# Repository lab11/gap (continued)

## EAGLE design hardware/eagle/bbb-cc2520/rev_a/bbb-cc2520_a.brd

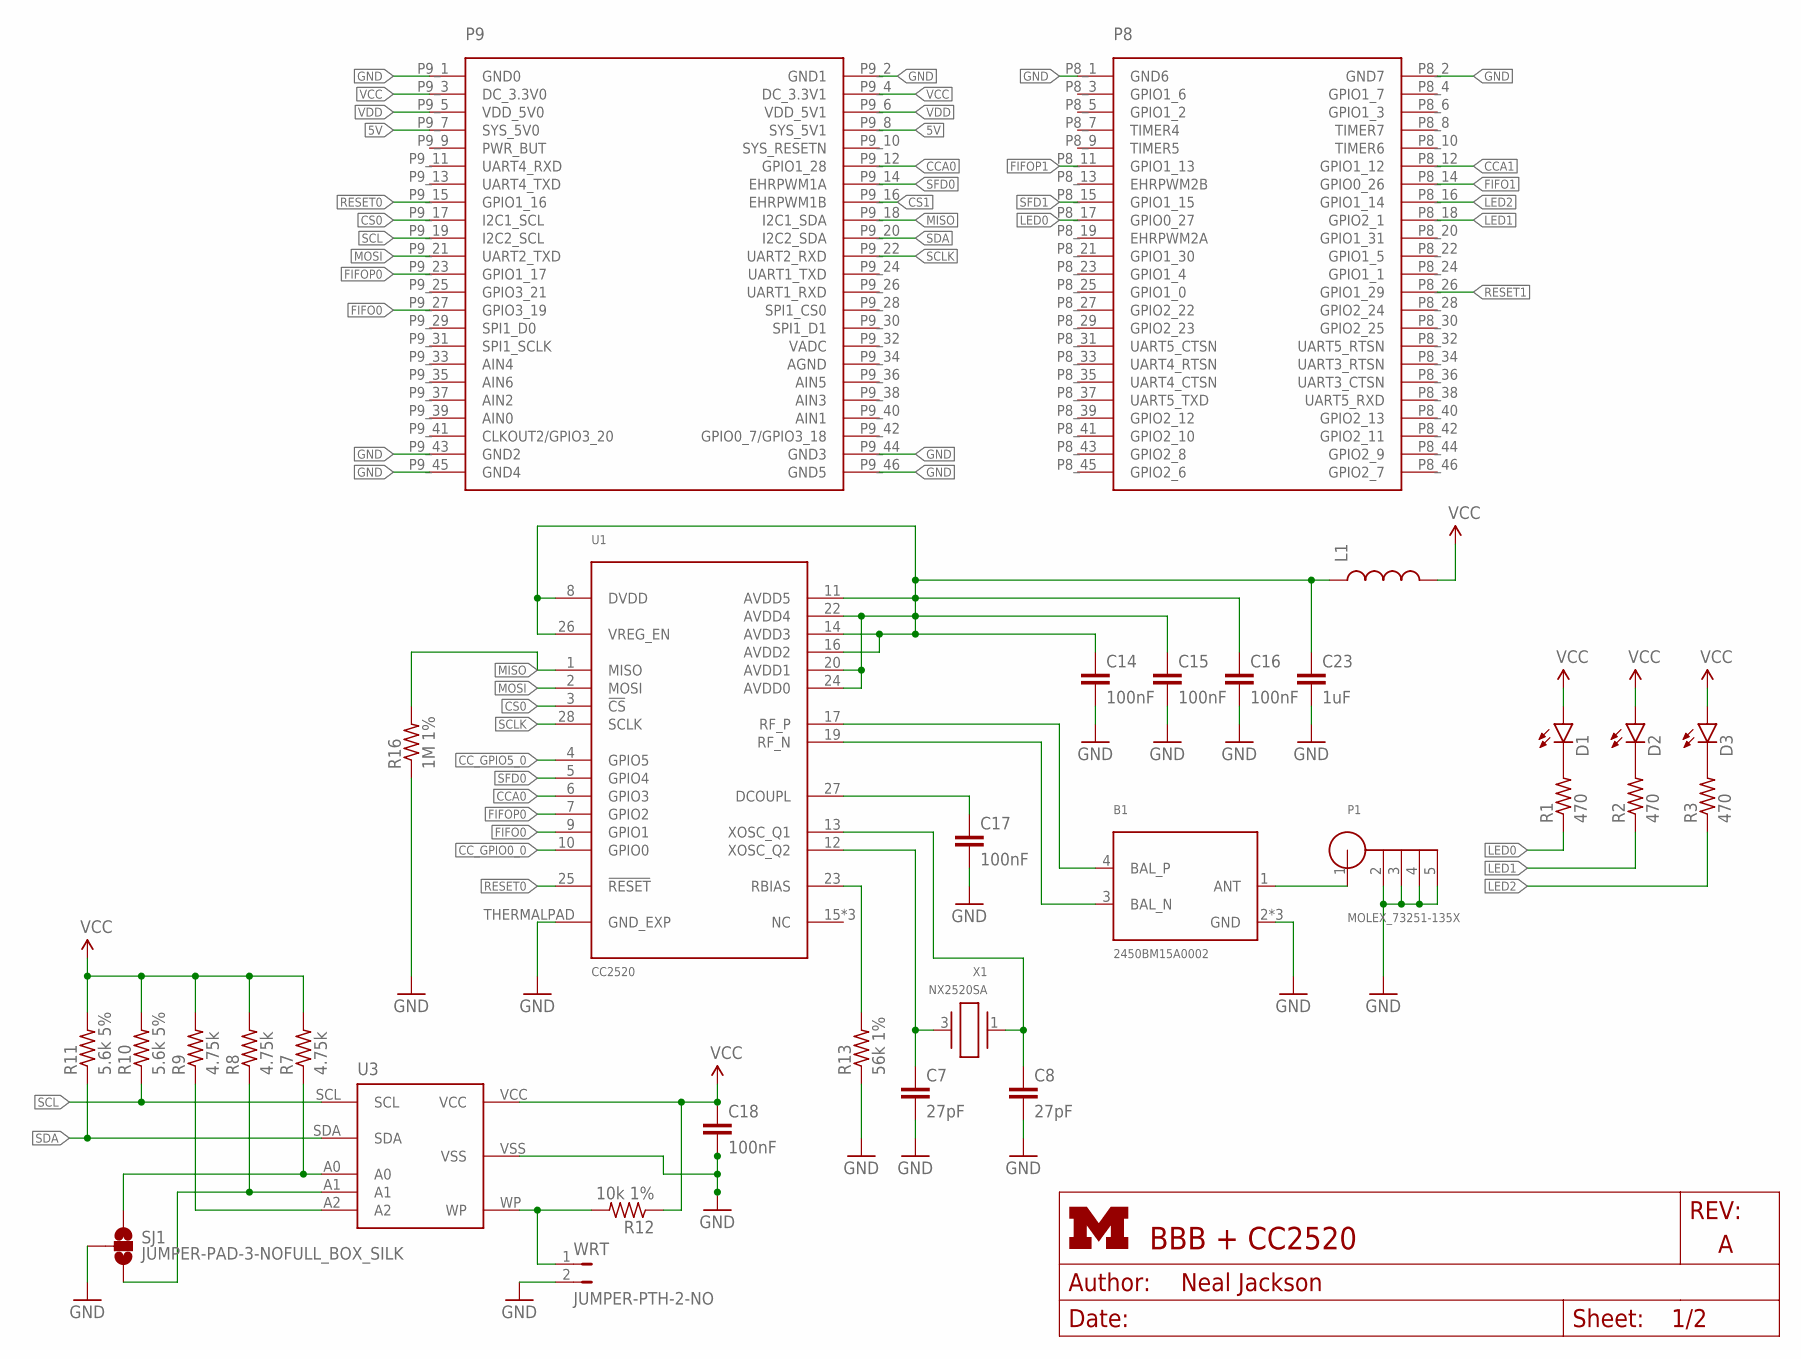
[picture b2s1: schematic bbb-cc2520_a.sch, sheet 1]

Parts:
B1: 2450BM15A0002; 2450BM
C7, C8: 27pF; C0402; DIGIKEY 490-5869-1-ND
C14, C15, C16, C17, C18: 100nF; C0402; DIGIKEY 490-1318-1-ND
C23: 1uF; C0603; DIGIKEY 490-1550-1-ND
D1: LED0603; LED-0603; DIGIKEY 160-1834-1-ND
D2: LED0603; LED-0603; DIGIKEY 160-1835-1-ND
D3: LED0603; LED-0603; DIGIKEY 160-1837-1-ND
L1: INDUCTOR0603; 0603; DIGIKEY 490-1015-1-ND
P1: MOLEX_73251-135X; SMA-J/PCB
P9/P8: BBB_HEADERS
R1, R2, R3: 470; R0402; DIGIKEY RHM470JCT-ND
R7, R8, R9: 4.75k; R0402; DIGIKEY RHM1.00MCDCT-ND
R10, R11: 5.6k 5%; R0402; DIGIKEY RHM1.00MCDCT-ND
R12: 10k 1%; R0402; DIGIKEY RHM1.00MCDCT-ND
R13: 56k 1%; R0402; DIGIKEY P56.0KLCT-ND
R16: 1M 1%; R0402; DIGIKEY RHM1.00MCDCT-ND
SJ1: JUMPER-PAD-3-NOFULL_BOX_SILK; PAD-JUMPER-3-NO_YES_SILK_FULL_BOX
U1: CC2520; S-PVQFN-N28
U3: CAT24C256WI-GT3
WRT: JUMPER-PTH-2-NO; PTH-JUMPER-2-NO_NO_SILK
X1: NX2520SA

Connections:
5V: P9/P8.P9_7 (SYS_5V0), P9/P8.P9_8 (SYS_5V1)
!RESET0: P9/P8.P9_15 (GPIO1_16), U1.25 (!RESET)
!RESET1: P9/P8.P8_26 (GPIO1_29); also elsewhere on the board
CCA0: P9/P8.P9_12 (GPIO1_28), U1.6 (GPIO3)
CCA1: P9/P8.P8_12 (GPIO1_12); also elsewhere on the board
CC_GPIO0_0: U1.10 (GPIO0)
CC_GPIO5_0: U1.4 (GPIO5)
CS0: P9/P8.P9_17 (I2C1_SCL), U1.3 (!CS)
CS1: P9/P8.P9_16 (EHRPWM1B); also elsewhere on the board
FIFO0: P9/P8.P9_27 (GPIO3_19), U1.9 (GPIO1)
FIFO1: P9/P8.P8_14 (GPIO0_26); also elsewhere on the board
FIFOP0: P9/P8.P9_23 (GPIO1_17), U1.7 (GPIO2)
FIFOP1: P9/P8.P8_11 (GPIO1_13); also elsewhere on the board
GND: B1.2 (GND), B1.5 (GND), B1.6 (GND), C7.2, C8.2, C14.2, C15.2, C16.2, C17.2, C18.2, C23.2, P1.2, P1.3, P1.4, P1.5, P9/P8.P8_1 (GND6), P9/P8.P8_2 (GND7), P9/P8.P9_1 (GND0), P9/P8.P9_2 (GND1), P9/P8.P9_43 (GND2), P9/P8.P9_44 (GND3), P9/P8.P9_45 (GND4), P9/P8.P9_46 (GND5), R13.1, R16.1, SJ1.2, U1.THERMALPAD (GND_EXP), U3.VSS, WRT.2; also elsewhere on the board
LED0: P9/P8.P8_17 (GPIO0_27), R1.1
LED1: P9/P8.P8_18 (GPIO2_1), R2.1
LED2: P9/P8.P8_16 (GPIO1_14), R3.1
MISO: P9/P8.P9_18 (I2C1_SDA), R16.2, U1.1 (MISO); also elsewhere on the board
MOSI: P9/P8.P9_21 (UART2_TXD), U1.2 (MOSI); also elsewhere on the board
unnamed: D1.C, R1.2
unnamed: D2.C, R2.2
unnamed: D3.C, R3.2
unnamed: C14.1, C15.1, C16.1, C23.1, L1.1, U1.8 (DVDD), U1.11 (AVDD5), U1.14 (AVDD3), U1.16 (AVDD2), U1.20 (AVDD1), U1.22 (AVDD4), U1.24 (AVDD0), U1.26 (VREG_EN)
unnamed: B1.1 (ANT), P1.1
unnamed: C8.1, U1.13 (XOSC_Q1), X1.1
unnamed: C17.1, U1.27 (DCOUPL)
unnamed: C7.1, U1.12 (XOSC_Q2), X1.3 (2)
unnamed: R13.2, U1.23 (RBIAS)
unnamed: R7.1, SJ1.1, U3.A0
unnamed: R8.1, SJ1.3, U3.A1
unnamed: R12.2, U3.WP, WRT.1
unnamed: R9.1, U3.A2
RF_N: B1.3 (BAL_N), U1.19 (RF_N)
RF_P: B1.4 (BAL_P), U1.17 (RF_P)
SCL: P9/P8.P9_19 (I2C2_SCL), R10.1, U3.SCL
SCLK: P9/P8.P9_22 (UART2_RXD), U1.28 (SCLK); also elsewhere on the board
SDA: P9/P8.P9_20 (I2C2_SDA), R11.1, U3.SDA
SFD0: P9/P8.P9_14 (EHRPWM1A), U1.5 (GPIO4)
SFD1: P9/P8.P8_15 (GPIO1_15); also elsewhere on the board
VCC: C18.1, D1.A, D2.A, D3.A, L1.2, P9/P8.P9_3 (DC_3.3V0), P9/P8.P9_4 (DC_3.3V1), R7.2, R8.2, R9.2, R10.2, R11.2, R12.1, U3.VCC; also elsewhere on the board
VDD: P9/P8.P9_5 (VDD_5V0), P9/P8.P9_6 (VDD_5V1)

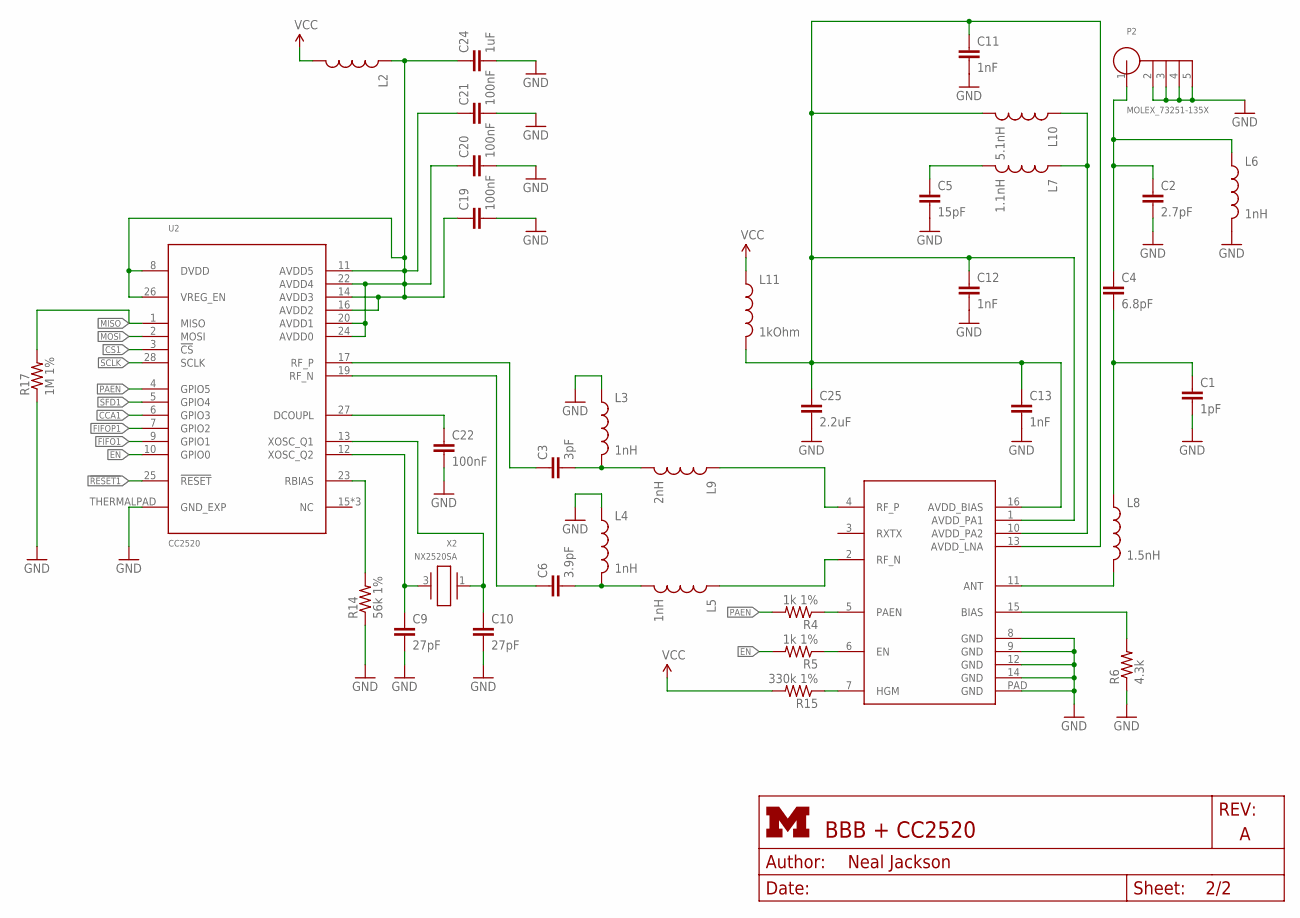
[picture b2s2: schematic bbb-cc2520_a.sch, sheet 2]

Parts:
C1: 1pF; C0402; DIGIKEY 490-1318-1-ND
C2: 2.7pF; C0402; DIGIKEY 490-1318-1-ND
C3: 3pF; C0402; DIGIKEY 490-1318-1-ND
C4: 6.8pF; C0402; DIGIKEY 490-1318-1-ND
C5: 15pF; C0402; DIGIKEY 490-1318-1-ND
C6: 3.9pF; C0402; DIGIKEY 490-1318-1-ND
C9, C10: 27pF; C0402; DIGIKEY 490-5869-1-ND
C11, C12, C13: 1nF; C0402; DIGIKEY 490-1318-1-ND
C19, C20, C21, C22: 100nF; C0402; DIGIKEY 490-1318-1-ND
C24: 1uF; C0603; DIGIKEY 490-1550-1-ND
C25: 2.2uF; C0402; DIGIKEY 490-1318-1-ND
L2: INDUCTOR0603; 0603; DIGIKEY 490-1015-1-ND
L3, L4, L5, L6: 1nH; C0402
L7: 1.1nH; C0402
L8: 1.5nH; C0402
L9: 2nH; C0402
L10: 5.1nH; C0402
L11: 1kOhm; C0402
P2: MOLEX_73251-135X; SMA-J/PCB
R4, R5: 1k 1%; R0402; DIGIKEY P56.0KLCT-ND
R6: 4.3k; R0402; DIGIKEY P56.0KLCT-ND
R14: 56k 1%; R0402; DIGIKEY P56.0KLCT-ND
R15: 330k 1%; R0402; DIGIKEY P56.0KLCT-ND
R17: 1M 1%; R0402; DIGIKEY RHM1.00MCDCT-ND
U2: CC2520; S-PVQFN-N28
U4: CC2591; PVQFN-16
X2: NX2520SA

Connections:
!RESET1: U2.25 (!RESET); also elsewhere on the board
CCA1: U2.6 (GPIO3); also elsewhere on the board
CS1: U2.3 (!CS); also elsewhere on the board
EN: R5.2, U2.10 (GPIO0)
FIFO1: U2.9 (GPIO1); also elsewhere on the board
FIFOP1: U2.7 (GPIO2); also elsewhere on the board
GND: C1.2, C2.2, C5.2, C9.2, C10.2, C11.2, C12.2, C13.2, C19.2, C20.2, C21.2, C22.2, C24.2, C25.2, L3.1, L4.1, L6.2, P2.2, P2.3, P2.4, P2.5, R6.1, R14.1, R17.1, U2.THERMALPAD (GND_EXP), U4.8 (GND), U4.9 (GND), U4.12 (GND), U4.14 (GND), U4.PAD (GND); also elsewhere on the board
MISO: R17.2, U2.1 (MISO); also elsewhere on the board
MOSI: U2.2 (MOSI); also elsewhere on the board
unnamed: L9.1, U4.4 (RF_P)
unnamed: L5.1, U4.2 (RF_N)
unnamed: C6.2, L4.2, L5.2
unnamed: C3.2, L3.2, L9.2
unnamed: L7.1, L10.1, U4.10 (AVDD_PA2)
unnamed: C11.1, C12.1, C13.1, C25.1, L10.2, L11.2, U4.1 (AVDD_PA1), U4.13 (AVDD_LNA), U4.16 (AVDD_BIAS)
unnamed: C5.1, L7.2
unnamed: L8.2, U4.11 (ANT)
unnamed: C2.1, C4.1, L6.1, P2.1
unnamed: C1.1, C4.2, L8.1
unnamed: R6.2, U4.15 (BIAS)
unnamed: R4.1, U4.5 (PAEN)
unnamed: R5.1, U4.6 (EN)
unnamed: C19.1, C20.1, C21.1, C24.1, L2.1, U2.8 (DVDD), U2.11 (AVDD5), U2.14 (AVDD3), U2.16 (AVDD2), U2.20 (AVDD1), U2.22 (AVDD4), U2.24 (AVDD0), U2.26 (VREG_EN)
unnamed: C22.1, U2.27 (DCOUPL)
unnamed: C10.1, U2.13 (XOSC_Q1), X2.1
unnamed: C9.1, U2.12 (XOSC_Q2), X2.3 (2)
unnamed: R14.2, U2.23 (RBIAS)
unnamed: R15.1, U4.7 (HGM)
PAEN: R4.2, U2.4 (GPIO5)
RF_N2: C6.1, U2.19 (RF_N)
RF_P2: C3.1, U2.17 (RF_P)
SCLK: U2.28 (SCLK); also elsewhere on the board
SFD1: U2.5 (GPIO4); also elsewhere on the board
VCC: L2.2, L11.1, R15.2; also elsewhere on the board

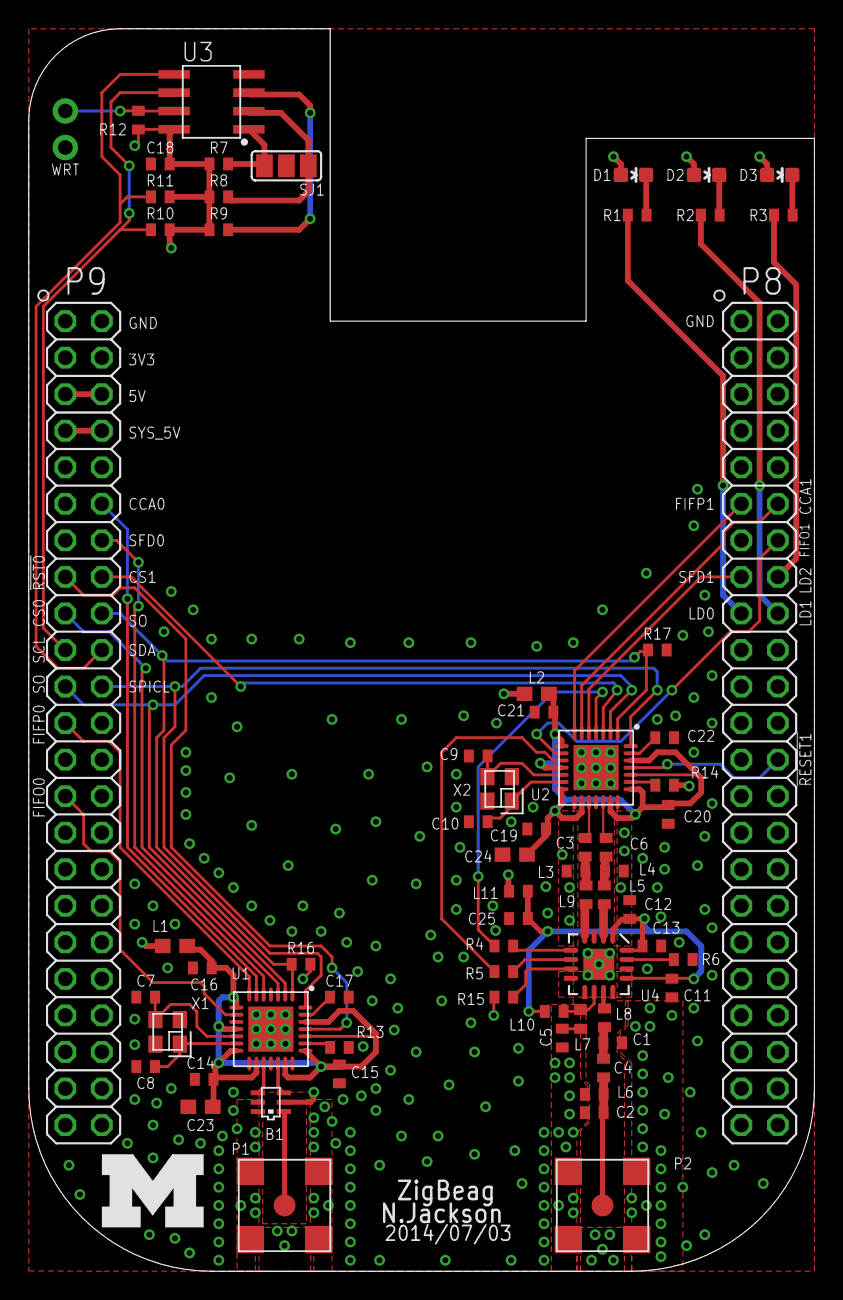
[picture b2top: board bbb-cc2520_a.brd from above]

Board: 4 copper layers, 54.6 x 86.4 mm, 69 parts (0 on the bottom side), 62 nets.

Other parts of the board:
U$2: UMICH_SOLID_200MIL

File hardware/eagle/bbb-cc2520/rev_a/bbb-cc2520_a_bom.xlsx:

Qty | Value | Device | Package | Parts | Description | DIGIKEY | SAMTEC | MAJOR LEAGUE | Manufacturer part number: | Comments
1 | 2450BM15A0002 | 2450BM15A0002 | 2450BM | B1 | BALUN JTI MATCHED ZIGBEE | 712-1536-1-ND |  |  | 2450BM15A0002E
1 | 1pF | C-EUC0402 | C0402 | C1 | Capacitor, 1p, 0402, NP0, +/-0.1pF 50V | 490-6206-1-ND |  |  | GRM1555C1H1R0BA01D | Original part number: GRM1555C1H1R0BZ01D
3 | 1nF | C-EUC0402 | C0402 | C11, C12, C13 | Capacitor, 1n, 0402, NP0, 5%, 50V | 490-3244-1-ND |  |  | GRM1555C1H102JA01D
9 | 100nF | C-EUC0402 | C0402 | C14, C15, C16, C17, C18, C19, C20, C21, C22 | Capacitor, 100n, 0402, X5R, 10%, 10V | 490-1318-1-ND |  |  | GRM155R61A104KA01D
1 | 2.7pF | C-EUC0402 | C0402 | C2 | Capacitor, 2p7, 0402, NP0, +-0.25pF, 50V | 490-5934-1-ND |  |  | GRM1555C1H2R7CA01D | Original part number: GRM1555C1H2R7CZ01D
2 | 1uF | C-EUC0603 | C0603 | C23, C24 | Capacitor, 1u0, 0402, X5R, 10%, 6.3V | 490-1550-1-ND |  |  | GRM188R60J105KA01D
1 | 2.2uF | C-EUC0402 | C0402 | C25 | Capacitor, 2u2, 0402, X5R, 20%, 4V | 490-4518-1-ND |  |  | GRM155R60G225ME15D | Using a 4v instead of reference design 6.3
1 | 3pF | C-EUC0402 | C0402 | C3 | Capacitor, 3p, 0402, NP0, +-0.25pF, 50V | 490-5872-1-ND |  |  | GRM1555C1H3R0CA01D | Original part number: GRM1555C1H3R0CZ01D
1 | 6.8pF | C-EUC0402 | C0402 | C4 | Capacitor, 6p8, 0402, NP0, +-0.25pF 50V | 490-5949-1-ND |  |  | GRM1555C1H6R8CA01D | Original part number: GRM1555C1H6R8CZ01D
1 | 15pF | C-EUC0402 | C0402 | C5 | Capacitor, 15p, 0402, NP0, 5%, 50V | 490-5888-1-ND |  |  | GRM1555C1H150JA01D | Original part number: GRM1555C1H150JZ01D
1 | 3.9pF | C-EUC0402 | C0402 | C6 | Capacitor, 3p9, 0402, NP0, +-0.25pF, 50V | 490-1272-1-ND |  |  | GRM1555C1H3R9CZ01D
4 | 27pF | C-EUC0402 | C0402 | C7, C8, C9, C10 | Capacitor, 27p, 0402, NP0, 5%, 50V | 490-5869-1-ND |  |  | GRM1555C1H270JA01D | Original part number: GRM1555C1H270JZ01D
1 |  | LED0603 | LED-0603 | D1 | LEDs | 160-1834-1-ND
1 |  | LED0603 | LED-0603 | D2 | LEDs | 160-1835-1-ND
1 |  | LED0603 | LED-0603 | D3 | LEDs | 160-1837-1-ND
2 | 1k Ohm | INDUCTOR0603 | L0603 | L1, L2 | EMI filter bead, 0603 1Kohms GHz Band Gen Use | 490-1015-1-ND
1 | 5.1nH | INDUCTOR0402 | C0402 | L10 | Inductor, 5n1, 0402, +/-0.3 nH | 490-6573-1-ND |  |  | LQG15HS5N1S02D
1 | 1k Ohm | INDUCTOR0402 | C0402 | L11 | EMI filter bead, 0402 1Kohms GHz Band Gen Use | 490-3999-1-ND |  |  | BLM15HG102SN1D
4 | 1nH | INDUCTOR0402 | C0402 | L3, L4, L5, L6 | Inductor, 1n0, 0402, Monolithic type, +/-0.3 nH | 490-2610-1-ND |  |  | LQG15HS1N0S02D
1 | 1.1nH | INDUCTOR0402 | C0402 | L7 | Inductor, 1n1, 0402, Monolithic type, +/-0.3 nH | 490-6567-1-ND |  |  | LQG15HS1N1S02D
1 | 1.5nH | INDUCTOR0402 | C0402 | L8 | Inductor, 1n5, 0402, wire-wound type, +/-0.1 nH | 490-6782-1-ND |  |  | LQW15AN1N5B00D
1 | 2nH | INDUCTOR0402 | C0402 | L9 | Inductor, 2n0, 0402, +/-0.3 nH | 490-6569-1-ND |  |  | LQG15HS2N0S02D
2 | MOLEX_73251-135X | MOLEX_73251-135X | SMA-J/PCB | P1, P2 | SMA JACK SMT 50 OHM | WM9357-ND
2 | BBB_HEADERS | BBB_HEADERS | BBB_HEADERS | P9, P8 | 2x23 Pin Header |  | SSW-123-03-T-D | SSHQ-123-D-08-G-LF | SSHQ-123-D-08-G-LF
3 | 470 | R-US_R0402 | R0402 | R1, R2, R3 | RESISTOR, American symbol | RHM470JCT-ND
2 | 5.6k 5% | R-US_R0402 | R0402 | R10, R11 | RESISTOR, American symbol | RHM5.6KCGCT-ND
1 | 10k 1% | R-US_R0402 | R0402 | R12 | RESISTOR, American symbol | RHM10.0KCDCT-ND
2 | 56k 1% | R-US_R0402 | R0402 | R13, R14 | RESISTOR, American symbol | P56.0KLCT-ND
1 | 330k 1% | R-US_R0402 | R0402 | R15 | RESISTOR, American symbol | RHM330KCFCT-ND
2 | 1M 1% | R-US_R0402 | R0402 | R16, R17 | RESISTOR, American symbol | RHM1.00MCDCT-ND
2 | 1k 1% | R-US_R0402 | R0402 | R4, R5 | RESISTOR, American symbol | RHM1.00KCDCT-ND
1 | 4.3k | R-US_R0402 | R0402 | R6 | RESISTOR, American symbol | 1276-4078-1-ND
3 | 4.75k | R-US_R0402 | R0402 | R7, R8, R9 | RESISTOR, American symbol | 1276-4083-1-ND
2 | CC2520 | CC2520 | S-PVQFN-N28 | U1, U2 | 2.4 GHZ IEEE 802.15.4/ZIGBEE® RF TRANSCEIVER | 296-22996-1-ND
1 | CAT24C256WI-GT3 | CAT24C256WI-GT3 | SOIC-8 | U3 | 256kb Serial CMOS EEPROM | CAT24C256WI-GT3OSCT-ND
1 | CC2591 | CC2591 | PVQFN-16 | U4 | 2.4GHz Range Extender | 296-23603-1-ND
1 | JUMPER-PTH-2-NO | JUMPER-PTH-2-NO | PTH-JUMPER-2-NO_NO_SILK | WRT | 2x1 Pin Header | SAM1081-02-ND | TSW-102-26-S-S
2 | NX2520SA | NX2520SA | NX2520SA | X1, X2 | CRYSTAL 32MHZ 10PF SMD | 644-1065-1-ND

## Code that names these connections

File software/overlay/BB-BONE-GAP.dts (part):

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                /* the pin header uses */

                /* CC2520 GPIO */
                "P9.14",       /* SFD0:  gpio1_18 */
                "P9.23",       /* FIFP0: gpio1_17 */
                "P9.27",       /* FIFO0: gpio3_19 */
                "P9.12",       /* RST0:  gpio1_28 */
                "P9.15",       /* CCA0:  gpio1_16 */

                "P8.15",       /* SFD1:  gpio1_15 */
                "P8.13",       /* FIFP1: gpio0_23 */
                "P8.16",       /* FIFO1: gpio1_14 */
                "P8.26",       /* RST1:  gpio1_29 */
                "P8.14",       /* CCA1:  gpio0_26 */

                /* NRF51822 GPIO */
                "P9.11",       /* RST2: uart4_rxd */
                "P9.16",       /* BIRQ: gpio1_19  */

                /* UART */
                "P9.24",       /* UART1_TXD: uart1_txd */
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                "P8.12",       /* SPIE1: gpio1_12 */

                /* LEDS */
                "P8.19",       /* LED0: gpio0_22  */
                "P8.17",       /* LED1: gpio0_27  */
                "P8.18",       /* LED2: gpio2_1   */

                /* the hardware ip uses */
                "gpio1_18",
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                        	spi-max-frequency = <8000000>;

                            num-csmux-pins = <2>;
                            csmux0-gpio = <&gpio2 13 0>;
                            csmux1-gpio = <&gpio2 12 0>;
                        };
                };
        };
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
                            num-radios  = <2>;

                            fifo0-gpio  = <&gpio4 19 0>;
                            fifop0-gpio = <&gpio2 17 0>;
                            sfd0-gpio   = <&gpio2 18 0>;
                            cca0-gpio   = <&gpio2 16 0>;
                            rst0-gpio   = <&gpio2 28 0>;

                            radio0-csmux = <0>;
                            radio0-amplified = <0>;

                            fifo1-gpio  = <&gpio2 14 0>;
                            fifop1-gpio = <&gpio1 23 0>;
                            sfd1-gpio   = <&gpio2 15 0>;
                            cca1-gpio   = <&gpio1 26 0>;
                            rst1-gpio   = <&gpio2 29 0>;

                            radio1-csmux = <1>;
                            radio1-amplified = <1>;
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
                            num-radios  = <1>;

                            interrupt0-gpio = <&gpio2 19 0>;
                            rst0-gpio = <&gpio1 30 0>;
                            radio0-csmux = <2>;

                            status = "okay";
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
                            led0 {
                                label = "gap:green:usr0";
                                gpios = <&gpio1 22 1>; /* Active low */
                                linux,default-trigger = "none";
                                default-state = "off";
                            };

                            led1 {
                                label = "gap:red:usr1";
                                gpios = <&gpio1 27 1>;
                                linux,default-trigger = "none";
                                default-state = "off";
                            };

                            led2 {
                                label = "gap:blue:usr2";
                                gpios = <&gpio3 1 1>;
                                linux,default-trigger = "none";
                                default-state = "off";
                            };
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
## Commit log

2014-06-30 Update README.md
    Added link to original raspi board
2014-06-30 Added beaglebone black cc2520 driver and DTO source
2014-06-30 updated description, copyright and license information
2014-06-30 added initial information on driver, board and tinyOS
2014-06-30 fixed table
2014-07-10 updated pin layout to better utilize primary GPIOs
2014-07-10 added compiled device tree overlay (.dtbo)
2014-07-10 added eeprom utility for flashing cape
2014-07-11 added secondary utility to flash specifically for this cape
2014-07-11 first iteration of eepromflasher.c
2014-07-11 fixed eepromflasher
2014-07-11 fixed board naming in eepromflasher
2014-07-14 fixed version number in eeprom flasher, eeprom is now valid and loads firmware
2014-07-15 changed pin assignments in driver to match new board
2014-07-15 compiled new driver with new pin config
2014-07-15 now releases gpio pins correctly
2014-07-16 got device tree overlay to load cc2520 driver instead of spidev on load
2014-07-16 added install script for DTO and driver
2014-07-16 Updated README with install instructions, removed old eeprom utility
2014-07-16 One radio down, one to go
2014-07-16 forgot to add schematic
2014-07-21 depmod only updates cc2520 driver, rather than all of them. Made copy calls verbose to make it clearer what the script is doing
2014-07-21 Changed pinout again. Now using a GPIO as chip select instead of the SPI one. This will allow more radios to interface to the SPI0.
2014-07-22 compiled most recent driver to reflect gpio and spi changes
2014-07-22 finished routing both radios, rf traces
2014-07-24 finished initial rev a board layout, changes may come soon
2014-07-24 fixed gpios not freed on module unload
2014-07-25 fixed labeling and vias
2014-07-28 fixed typos
2014-07-29 rev a finished, gerbers generated, bom done
2014-07-29 multiple radios can now be created, although only radio0 is functional
2014-07-29 compiled kernel driver
2014-07-29 restructured char device setup errors, began working on device specific semaphores
2014-07-31 interrupts now tied to device, still need to change other code over
2014-08-04 changed .dts to reflect pins for second radio. changed driver read spi to dynamically operate chip select, removed unnecessary gpio calls to cs
2014-08-04 irq now initialized on device open
2014-08-05 migrating rx over to using multiple devices
2014-08-05 migrate read to use multiple devices
2014-08-05 fixed stupid merge conflicts
2014-08-19 read and write now access radio0
2014-08-19 swapped spi d0 d1 to match board
2014-08-19 added .profile to install
2014-08-20 changed device tree overlay to swap SPI d0, d1. Added compiled read/write tests for radio0 and radio1
2014-08-25 removed gpio cs, does not work with d0/d1 swap
2014-08-26 began hardware rev b
2014-08-26 multidevice works with radio0, still need to test radio1
2014-09-18 revb mostly finished, need to add BLE chip
2014-09-19 reverted to not using gpio cs
2014-09-19 compiled driver
2014-09-23 tests compile in place, added executables
2014-10-18 start on kernel module for nrf51822
2014-10-19 RevB finished
2014-10-20 updated nrf51822 kernel driver
    can issue commands!
2014-10-21 driver seems to work
2014-10-21 cleaned up driver
2014-10-21 driver now working with revb hardware, radio0
2014-10-22 adding demo webpage
2014-10-22 skinny
2014-10-22 good start
2014-10-22 added rpl
2014-10-22 all 3 displaying packets
2014-10-22 logo
2014-10-22 clean up
2014-10-23 support polling
2014-10-23 demo ble packets work!
2014-10-23 updates to demo
2014-10-24 updated interface.c to allow multiple open()
    registers irqs in init() instead of open()
2014-10-24 radio 0
2014-10-24 compile with no flags
2014-10-24 fixed reset on radio start
2014-10-24 init reset to high
2014-10-24 enable amp
2014-10-24 update gpio polarity
    amplifier works now
2014-11-14 began work on gapspi driver
2014-11-14 added export_symbol statements for spi calls
2014-11-16 moved files around finally
    working towards a more stable state
2014-11-16 gapspi compiles
2014-11-16 gitignore
2014-11-16 add test for receiving advs
2014-11-16 nrf and gap drivers seem to work!
2014-11-16 better printout in nrf test
2014-11-16 updated makefiles
2014-11-17 slightly updated readme
    directions need work. kind of want to wait until things settle before
    committing new directions
2014-11-17 added app that runs on the nRF51822
2014-11-17 add test script for receiving websockets
2014-11-17 added gitignore
2014-11-17 request gapspi from nrf driver
2014-11-17 update cc2520 to use gapspi module
    change name to cc2520_[0,1]
2014-11-17 added label for bluetooth irq
2014-11-17 gapspi mux setting works
2014-11-17 two radios working!!
2014-11-17 clean up gapspi
2014-11-17 clean up cc2520
2014-11-17 cleanup nrf
2014-11-17 require gapspi for cc2520
2014-11-18 cleaning up cc2520 folder
2014-11-18 copy spi message buffers
    two radios don't conflict now
2014-11-18 expanded tx side
2014-11-18 updated symbol for demux, added test points
2014-11-18 updated device tree overlay to include new drivers
2014-11-18 update overlay
    - rename things
    - move gpios to correct blocks
    - setup leds
2014-11-18 removed compiled .dtbo
2014-11-18 changed eeprom flasher utility to reference new firmware name
2014-11-18 working on autoload drivers
    making drivers better
2014-11-18 update printf in cc2520
    better macro
2014-11-18 woo! can get parameter from dts
2014-11-19 refactor
    get rid of all arrays. make device struct per radio
2014-11-19 sack refactored
2014-11-19 refactor csma
2014-11-19 refactor lpl
2014-11-19 refactor checkpoint
2014-11-19 compiles after refactoring
    wowee
2014-11-19 working on getting get_named_gpio_to_work
2014-11-19 fix memset
    I think this will solve the null ptr problem
2014-11-19 compiles
2014-11-19 don't need platform
2014-11-19 remove commented code
2014-11-19 made changes to board in regards to issue 3
2014-11-19 cleaned up pcb
2014-11-19 working on making nrf51822 dynamic
2014-11-19 updated schematic
2014-11-19 demo
2014-11-19 create rev c
2014-11-19 restore rev b
2014-11-19 init spin lock
2014-11-19 working on getting gapspi in shape
2014-11-19 gapspi errors
2014-11-20 all three working again!
2014-11-20 remove led
2014-11-20 cleaned up SDA trace on eeprom
2014-11-20 board cleaned up
2014-11-20 slight change to schematic
2014-11-20 update readme with all of the driver changes
2014-11-20 added board stackup information
2014-11-20 ship rev c
2014-11-25 added eeprom instructions
2014-12-04 add gitignore
2014-12-10 changed file descriptor to /dev/nrf51822_0
2014-12-11 Changed softdevice to S120, added sudo commands (needed for ubuntu, at least)
2014-12-11 removed compiled tests in cc2520/tests
2014-12-24 updates to readme
2015-01-08 added uart1 pins to dts
2015-01-09 added pin number comments, reset and uart reservations
2015-01-09 updated eeprom pin config
2015-01-09 changed gpio0 to gpio1 for NRF reset
2015-01-13 changed default channel to 19, updated device file name removed outdated reload.sh from cc2520
2015-01-13 updated write.c, channel 19, device file name
2015-01-13 added Brad Campbell as author
2015-01-14 added support for hardware acks, sack disabled by default needs testing
2015-01-15 removed if statement for sack_tx_done, fixes kernel panic
2015-01-22 added ioctl to toggle address filtering
2015-02-10 working on new tunnel
2015-02-10 tunnel server passes one test
2015-02-27 device tree for using gap with linux drivers
    - need to change hw to use spi1 for cc2520s and spi0 for mux
2015-03-17 need to checkout 3.19
2015-03-19 make note about the kernel version
2015-04-04 rev d
2015-04-14 moved cs0 pin
2015-04-14 committing changes to gap
2015-06-12 mouse bites
2015-06-18 updated gap for linux 4.1
2015-10-22 created overlay for rev d board
    wow. that was hard.
2015-10-22 some doc
2015-10-23 rename overlay
2015-10-23 update readmes
2015-10-23 save pdf for rev d
2015-10-23 cleaning up kernel drivers folder
2015-10-23 clean up software folder
2015-10-23 separate overlay and instructions
2015-10-23 remove old device tree stuff and guides
2015-10-23 update eeprom creator
2015-10-23 remove old demo
    this is probably still good code, but won't really work anymore. If
    we need it we'll just have to dig it up on github.
2015-10-27 add note about border router to readme
2015-12-07 added photo to readme
2015-12-11 rough first pass on reading 15.4 packets in c
2015-12-11 cleaned up raw read script
2015-12-11 add note about raw script for reading
2015-12-11 read raw wpan0 script in python
2015-12-11 add note about python script
2016-06-17 add mounting plate for making BBB magnetic
